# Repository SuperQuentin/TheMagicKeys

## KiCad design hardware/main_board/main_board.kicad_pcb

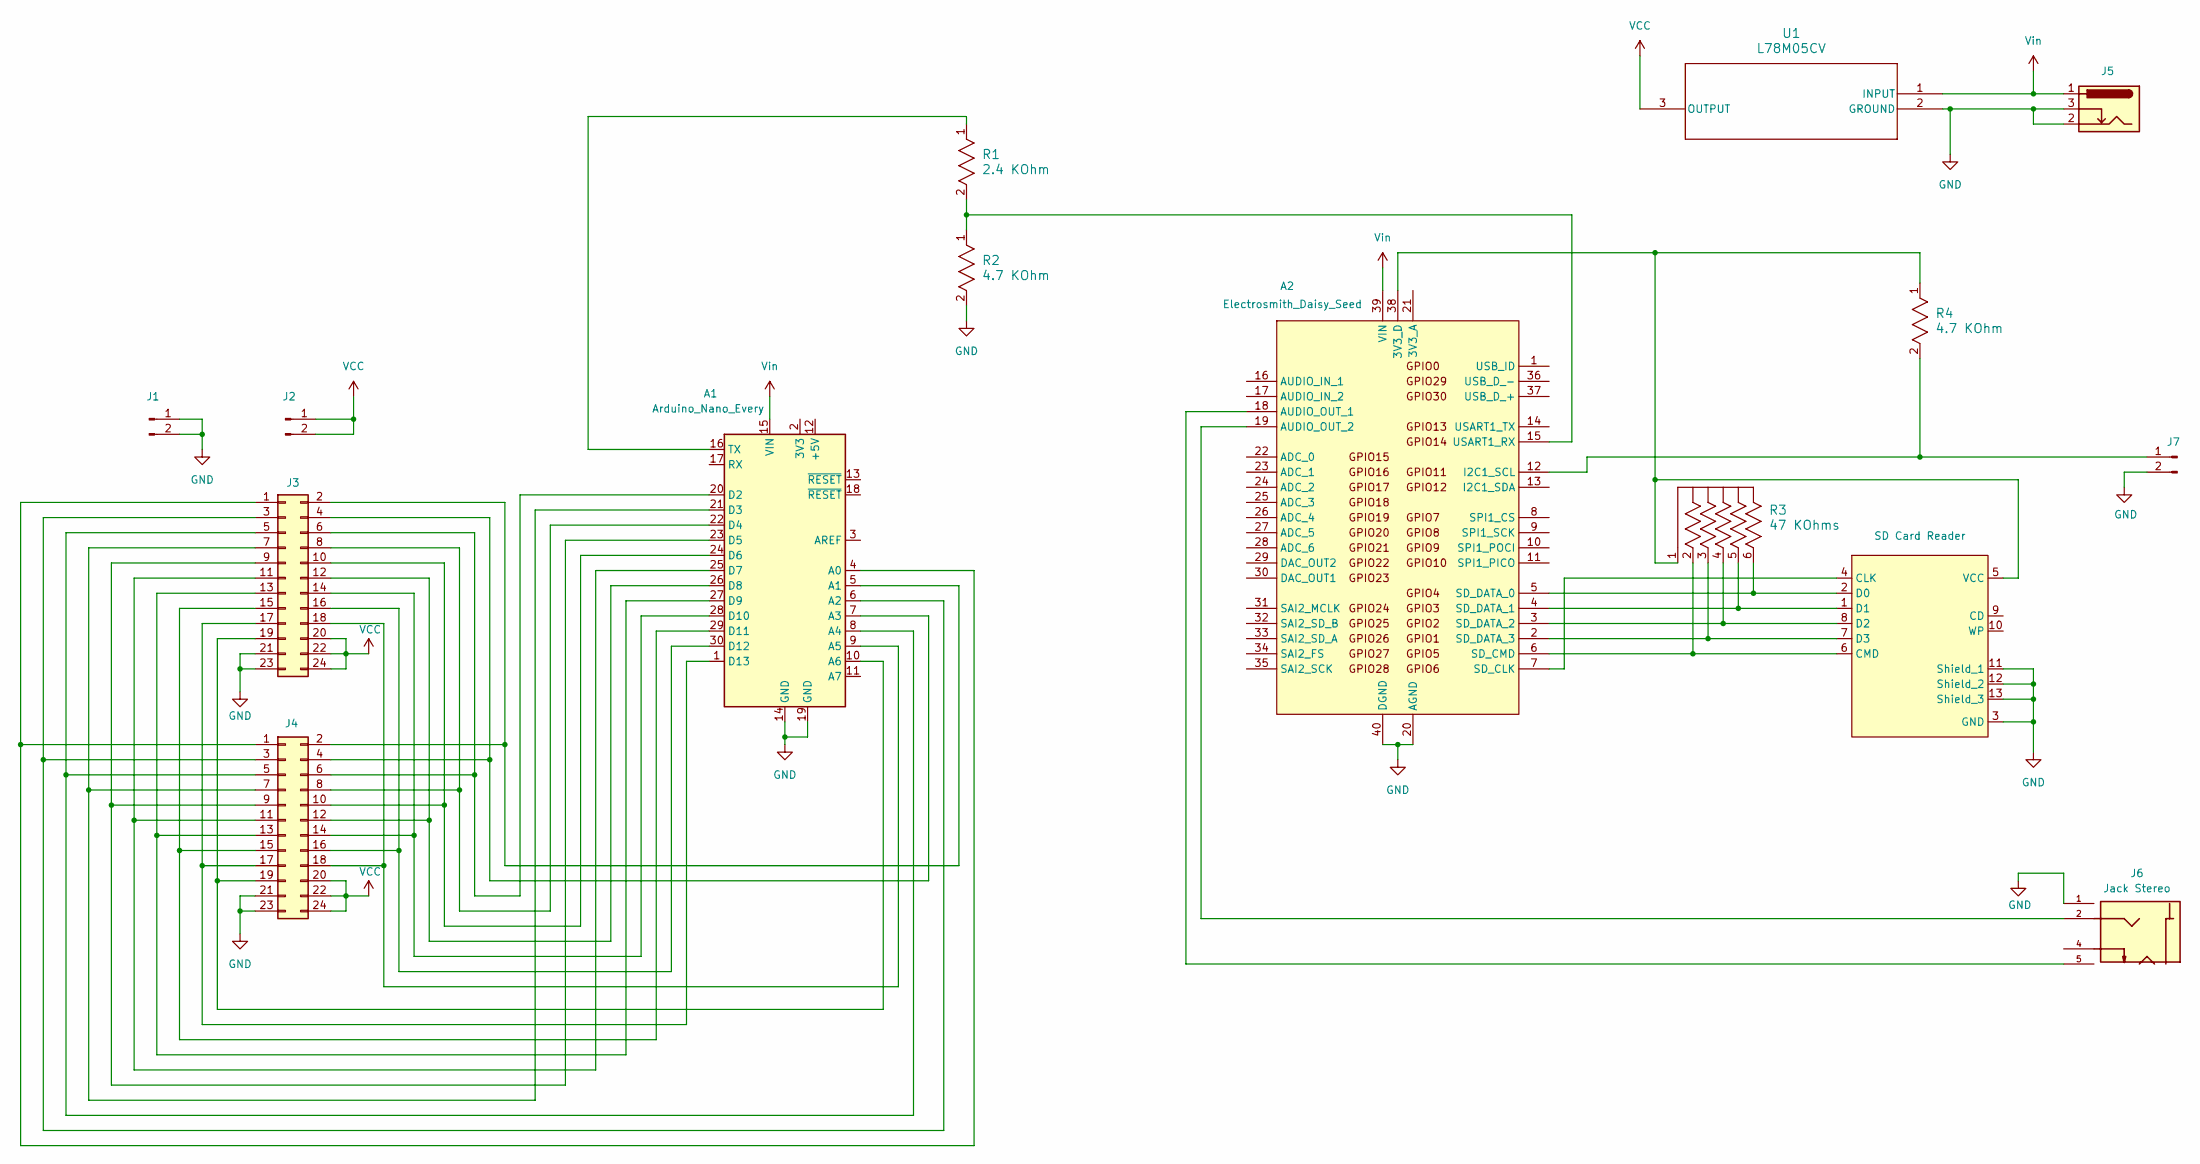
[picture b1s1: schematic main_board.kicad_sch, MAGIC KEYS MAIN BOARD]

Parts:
A1: Arduino_Nano_Every; Arduino_Nano
A2: Electrosmith_Daisy_Seed
J1, J2: PinHeader_2x01_P2.54mm_Vertical
J3, J4: Conn_02x12_Odd_Even; PinHeader_2x12_P2.54mm_Vertical
J5: Barrel_Jack_Switch_Pin2Ring; G-1005B
J6: Jack Stereo; SAMESKY_SJ3-35083C-TR; PARTREV 1.01
J7: Conn_01x02_Pin; PinHeader_1x02_P2.54mm_Vertical
R1: 2.4 KOhm; STA_CF14_STP
R2, R4: 4.7 KOhm; STA_CF14_STP
R3: 47 KOhms; BO_4606X
SDCardReaderBreakoutBoard1: SD Card Reader; SD_CARD_READER
U1: L78M05CV; TO-220_STM

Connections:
GND: A1.14 (GND), A1.19 (GND), A2.20 (AGND), A2.40 (DGND), J1.1, J1.2, J3.21, J3.23, J4.21, J4.23, J5.2, J5.3, J6.1, J7.2, R2.2, SDCardReaderBreakoutBoard1.3 (GND), SDCardReaderBreakoutBoard1.11 (Shield_1), SDCardReaderBreakoutBoard1.12 (Shield_2), SDCardReaderBreakoutBoard1.13 (Shield_3), U1.2 (GROUND)
unnamed: A1.4 (A0), J3.1, J4.1
unnamed: A1.5 (A1), J3.2, J4.2
unnamed: A1.6 (A2), J3.3, J4.3
unnamed: A1.7 (A3), J3.4, J4.4
unnamed: A1.8 (A4), J3.5, J4.5
unnamed: A1.9 (A5), J3.18, J4.18
unnamed: A1.10 (A6), J3.19, J4.19
unnamed: A1.20 (D2), J3.6, J4.6
unnamed: A1.21 (D3), J3.7, J4.7
unnamed: A1.22 (D4), J3.8, J4.8
unnamed: A1.23 (D5), J3.9, J4.9
unnamed: A1.24 (D6), J3.10, J4.10
unnamed: A1.25 (D7), J3.11, J4.11
unnamed: A1.26 (D8), J3.12, J4.12
unnamed: A1.27 (D9), J3.13, J4.13
unnamed: A1.28 (D10), J3.14, J4.14
unnamed: A1.29 (D11), J3.15, J4.15
unnamed: A1.30 (D12), J3.16, J4.16
unnamed: A1.1 (D13), J3.17, J4.17
unnamed: A1.16 (TX), R1.1
unnamed: A2.38 (3V3_D), R3.1, R4.1, SDCardReaderBreakoutBoard1.5 (VCC)
unnamed: A2.18 (AUDIO_OUT_1), J6.5
unnamed: A2.19 (AUDIO_OUT_2), J6.2
unnamed: A2.12 (I2C1_SCL), J7.1, R4.2
unnamed: A2.7 (SD_CLK), SDCardReaderBreakoutBoard1.4 (CLK)
unnamed: A2.6 (SD_CMD), R3.2, SDCardReaderBreakoutBoard1.6 (CMD)
unnamed: A2.5 (SD_DATA_0), R3.6, SDCardReaderBreakoutBoard1.2 (D0)
unnamed: A2.4 (SD_DATA_1), R3.5, SDCardReaderBreakoutBoard1.1 (D1)
unnamed: A2.3 (SD_DATA_2), R3.4, SDCardReaderBreakoutBoard1.8 (D2)
unnamed: A2.2 (SD_DATA_3), R3.3, SDCardReaderBreakoutBoard1.7 (D3)
unnamed: A2.15 (USART1_RX), R1.2, R2.1
VCC: J2.1, J2.2, J3.20, J3.22, J3.24, J4.20, J4.22, J4.24, U1.3 (OUTPUT)
Vin: A1.15 (VIN), A2.39 (VIN), J5.1, U1.1 (INPUT)

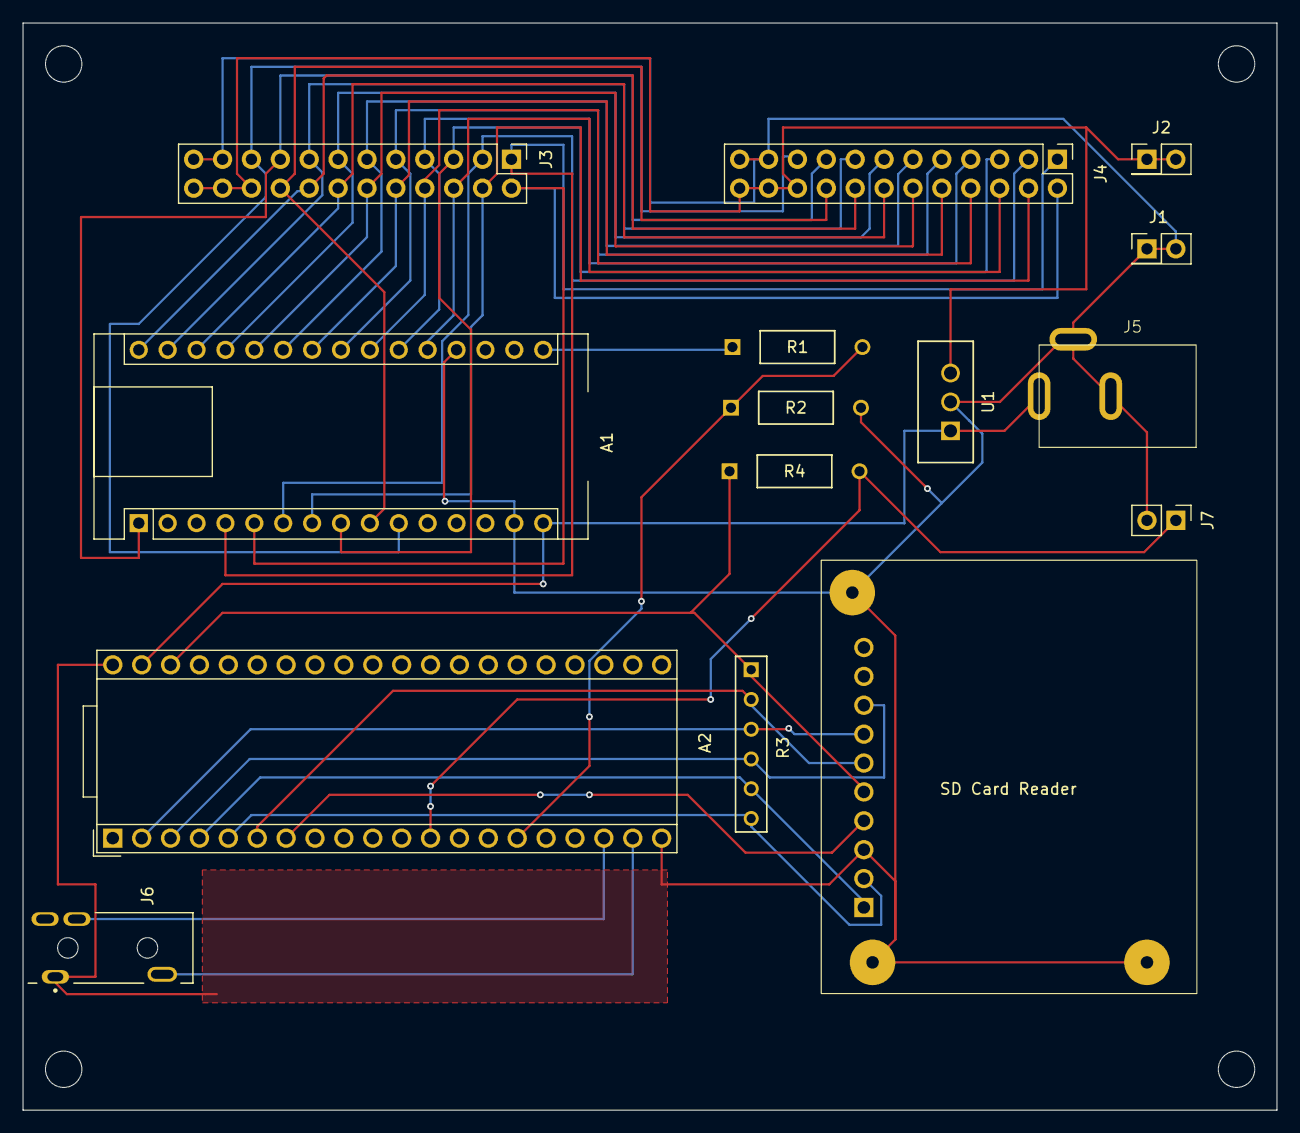
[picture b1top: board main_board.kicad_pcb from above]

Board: 2 copper layers, 110.3 x 95.6 mm, 15 parts (0 on the bottom side), 34 nets.

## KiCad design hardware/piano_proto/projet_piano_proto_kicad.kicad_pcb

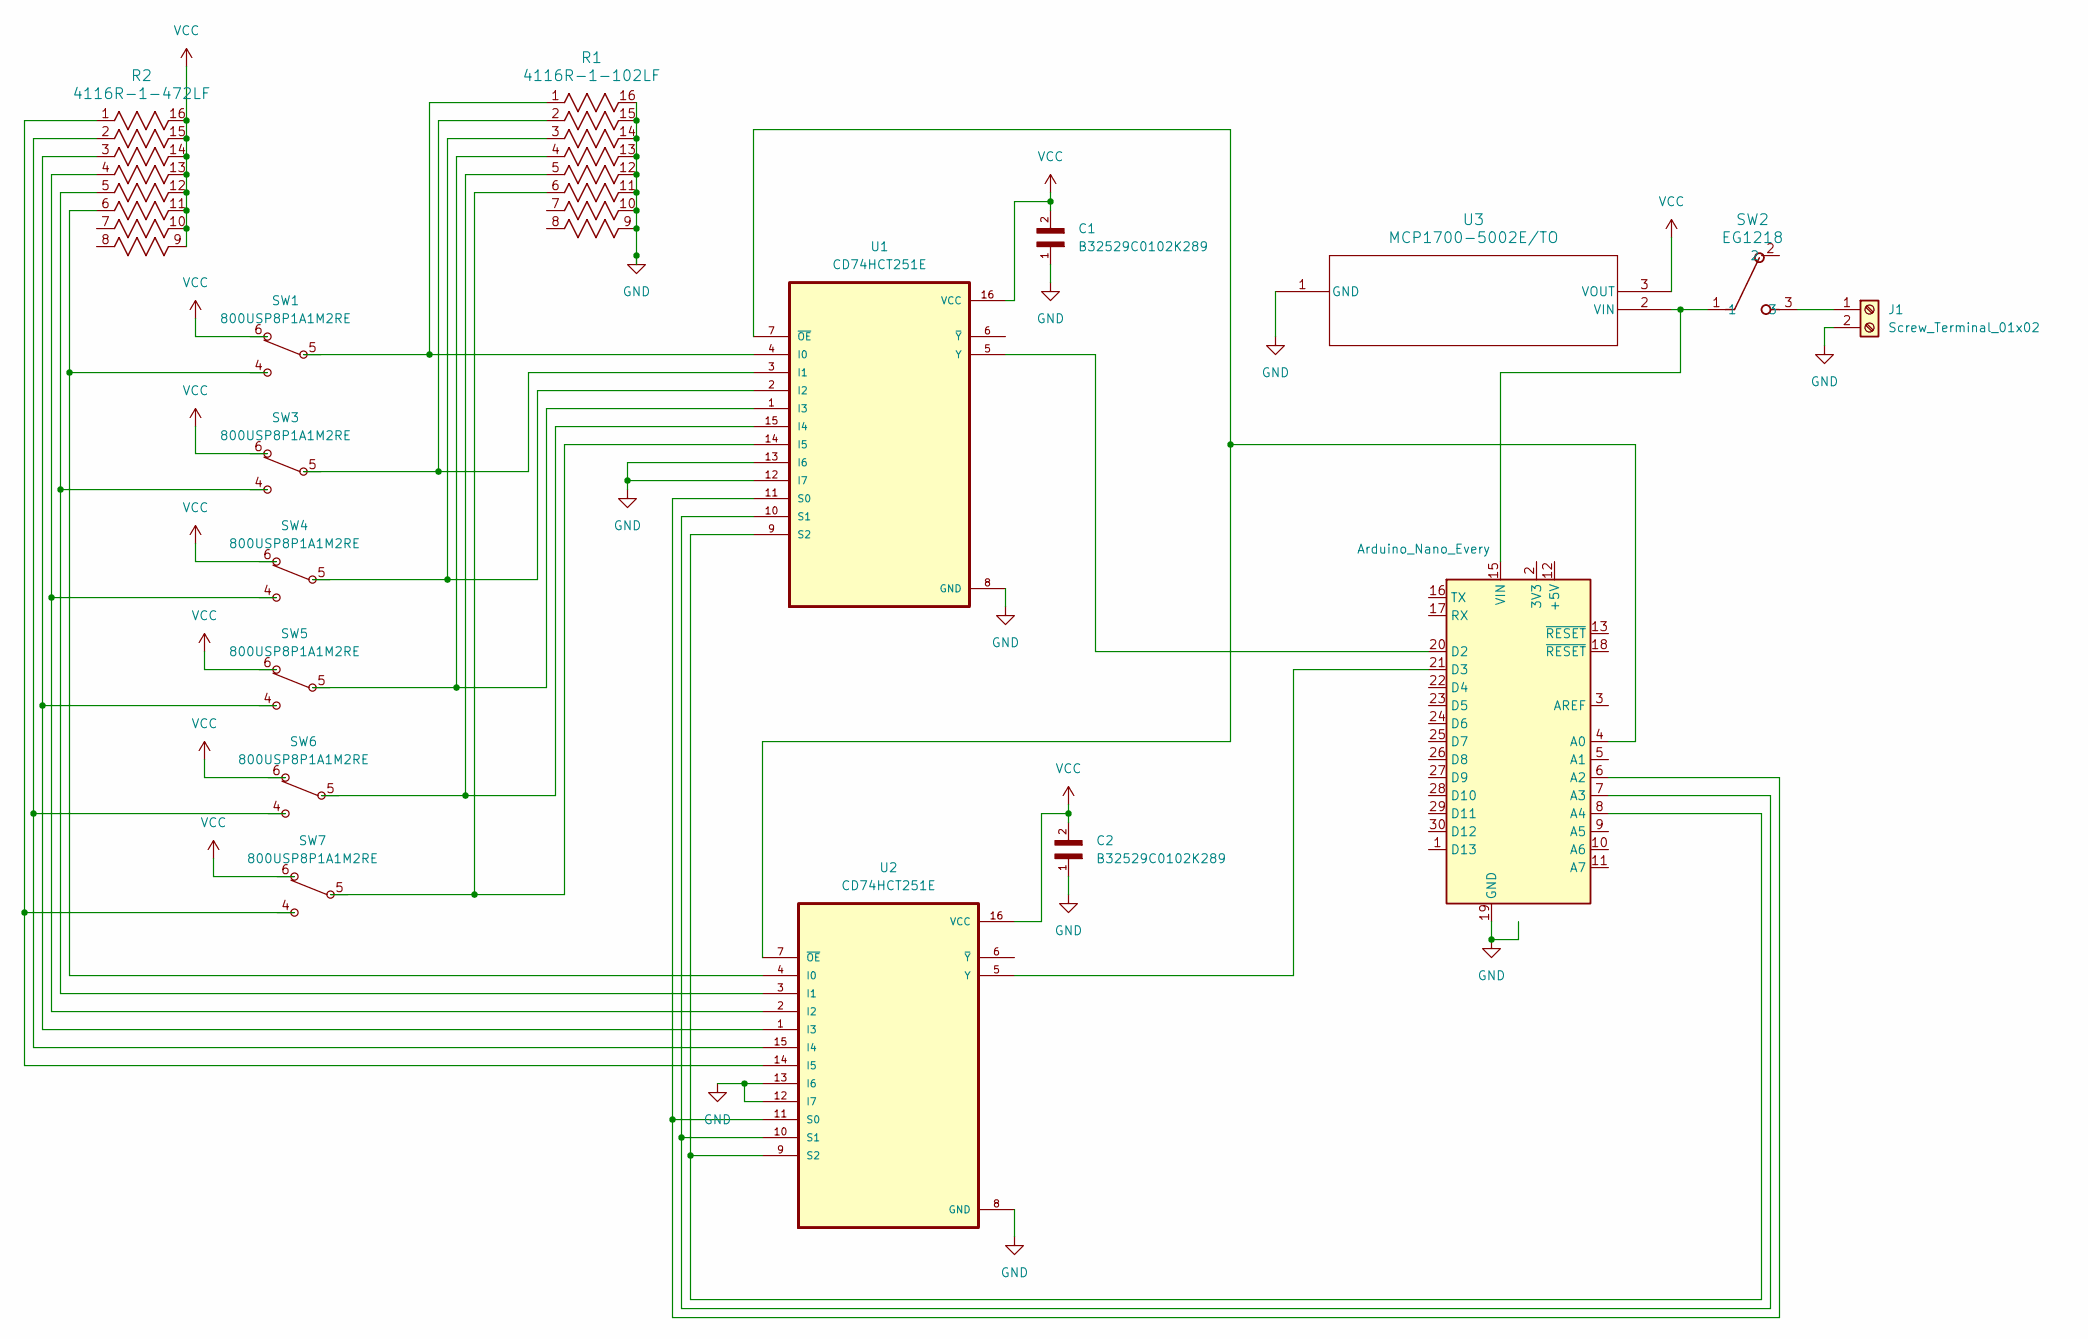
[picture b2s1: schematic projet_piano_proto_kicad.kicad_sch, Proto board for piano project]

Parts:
A2: Arduino_Nano_Every; Arduino_Nano
C1, C2: B32529C0102K289; CAPRR500W50L730T250H650; PARTREV 2020-06
J1: Screw_Terminal_01x02; TerminalBlock_Phoenix_MKDS-1,5-2-5.08_1x02_P5.08mm_Horizont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
R1: 4116R-1-102LF; BO_4116R
R2: 4116R-1-472LF; BO_4116R
SW1, SW3, SW4, SW5, SW6, SW7: 800USP8P1A1M2RE; Switch_Push_SPDT_800USP8P1A1M2RE
SW2: EG1218; SW_1218_EWI
U1, U2: CD74HCT251E; DIP794W45P254L1969H508Q16
U3: MCP1700-5002E/TO; TO-92_MC_MCH

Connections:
GND: A2.14 (GND), A2.19 (GND), C1.1, C2.1, J1.2, R1.9, R1.10, R1.11, R1.12, R1.13, R1.14, R1.15, R1.16, U1.8 (GND), U1.12 (I7), U1.13 (I6), U2.8 (GND), U2.12 (I7), U2.13 (I6), U3.1 (GND)
unnamed: A2.4 (A0), U1.7 (~OE), U2.7 (~OE)
unnamed: A2.6 (A2), U1.11 (S0), U2.11 (S0)
unnamed: A2.7 (A3), U1.10 (S1), U2.10 (S1)
unnamed: A2.20 (D2), U1.5 (Y)
unnamed: A2.21 (D3), U2.5 (Y)
unnamed: A2.8 (SDA/A4), U1.9 (S2), U2.9 (S2)
unnamed: A2.15 (VIN), SW2.1, U3.2 (VIN)
unnamed: J1.1, SW2.3
unnamed: R1.1, SW1.5 (COM), U1.4 (I0)
unnamed: R2.6, SW1.4 (NO), U2.4 (I0)
unnamed: R1.2, SW3.5 (COM), U1.3 (I1)
unnamed: R2.5, SW3.4 (NO), U2.3 (I1)
unnamed: R1.3, SW4.5 (COM), U1.2 (I2)
unnamed: R2.4, SW4.4 (NO), U2.2 (I2)
unnamed: R1.4, SW5.5 (COM), U1.1 (I3)
unnamed: R2.3, SW5.4 (NO), U2.1 (I3)
unnamed: R1.5, SW6.5 (COM), U1.15 (I4)
unnamed: R2.2, SW6.4 (NO), U2.15 (I4)
unnamed: R1.6, SW7.5 (COM), U1.14 (I5)
unnamed: R2.1, SW7.4 (NO), U2.14 (I5)
VCC: C1.2, C2.2, R2.9, R2.10, R2.11, R2.12, R2.13, R2.14, R2.15, R2.16, SW1.6 (NC), SW3.6 (NC), SW4.6 (NC), SW5.6 (NC), SW6.6 (NC), SW7.6 (NC), U1.16 (VCC), U2.16 (VCC), U3.3 (VOUT)

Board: 2 copper layers, 16 parts (0 on the bottom side), 22 nets, no tracks yet.

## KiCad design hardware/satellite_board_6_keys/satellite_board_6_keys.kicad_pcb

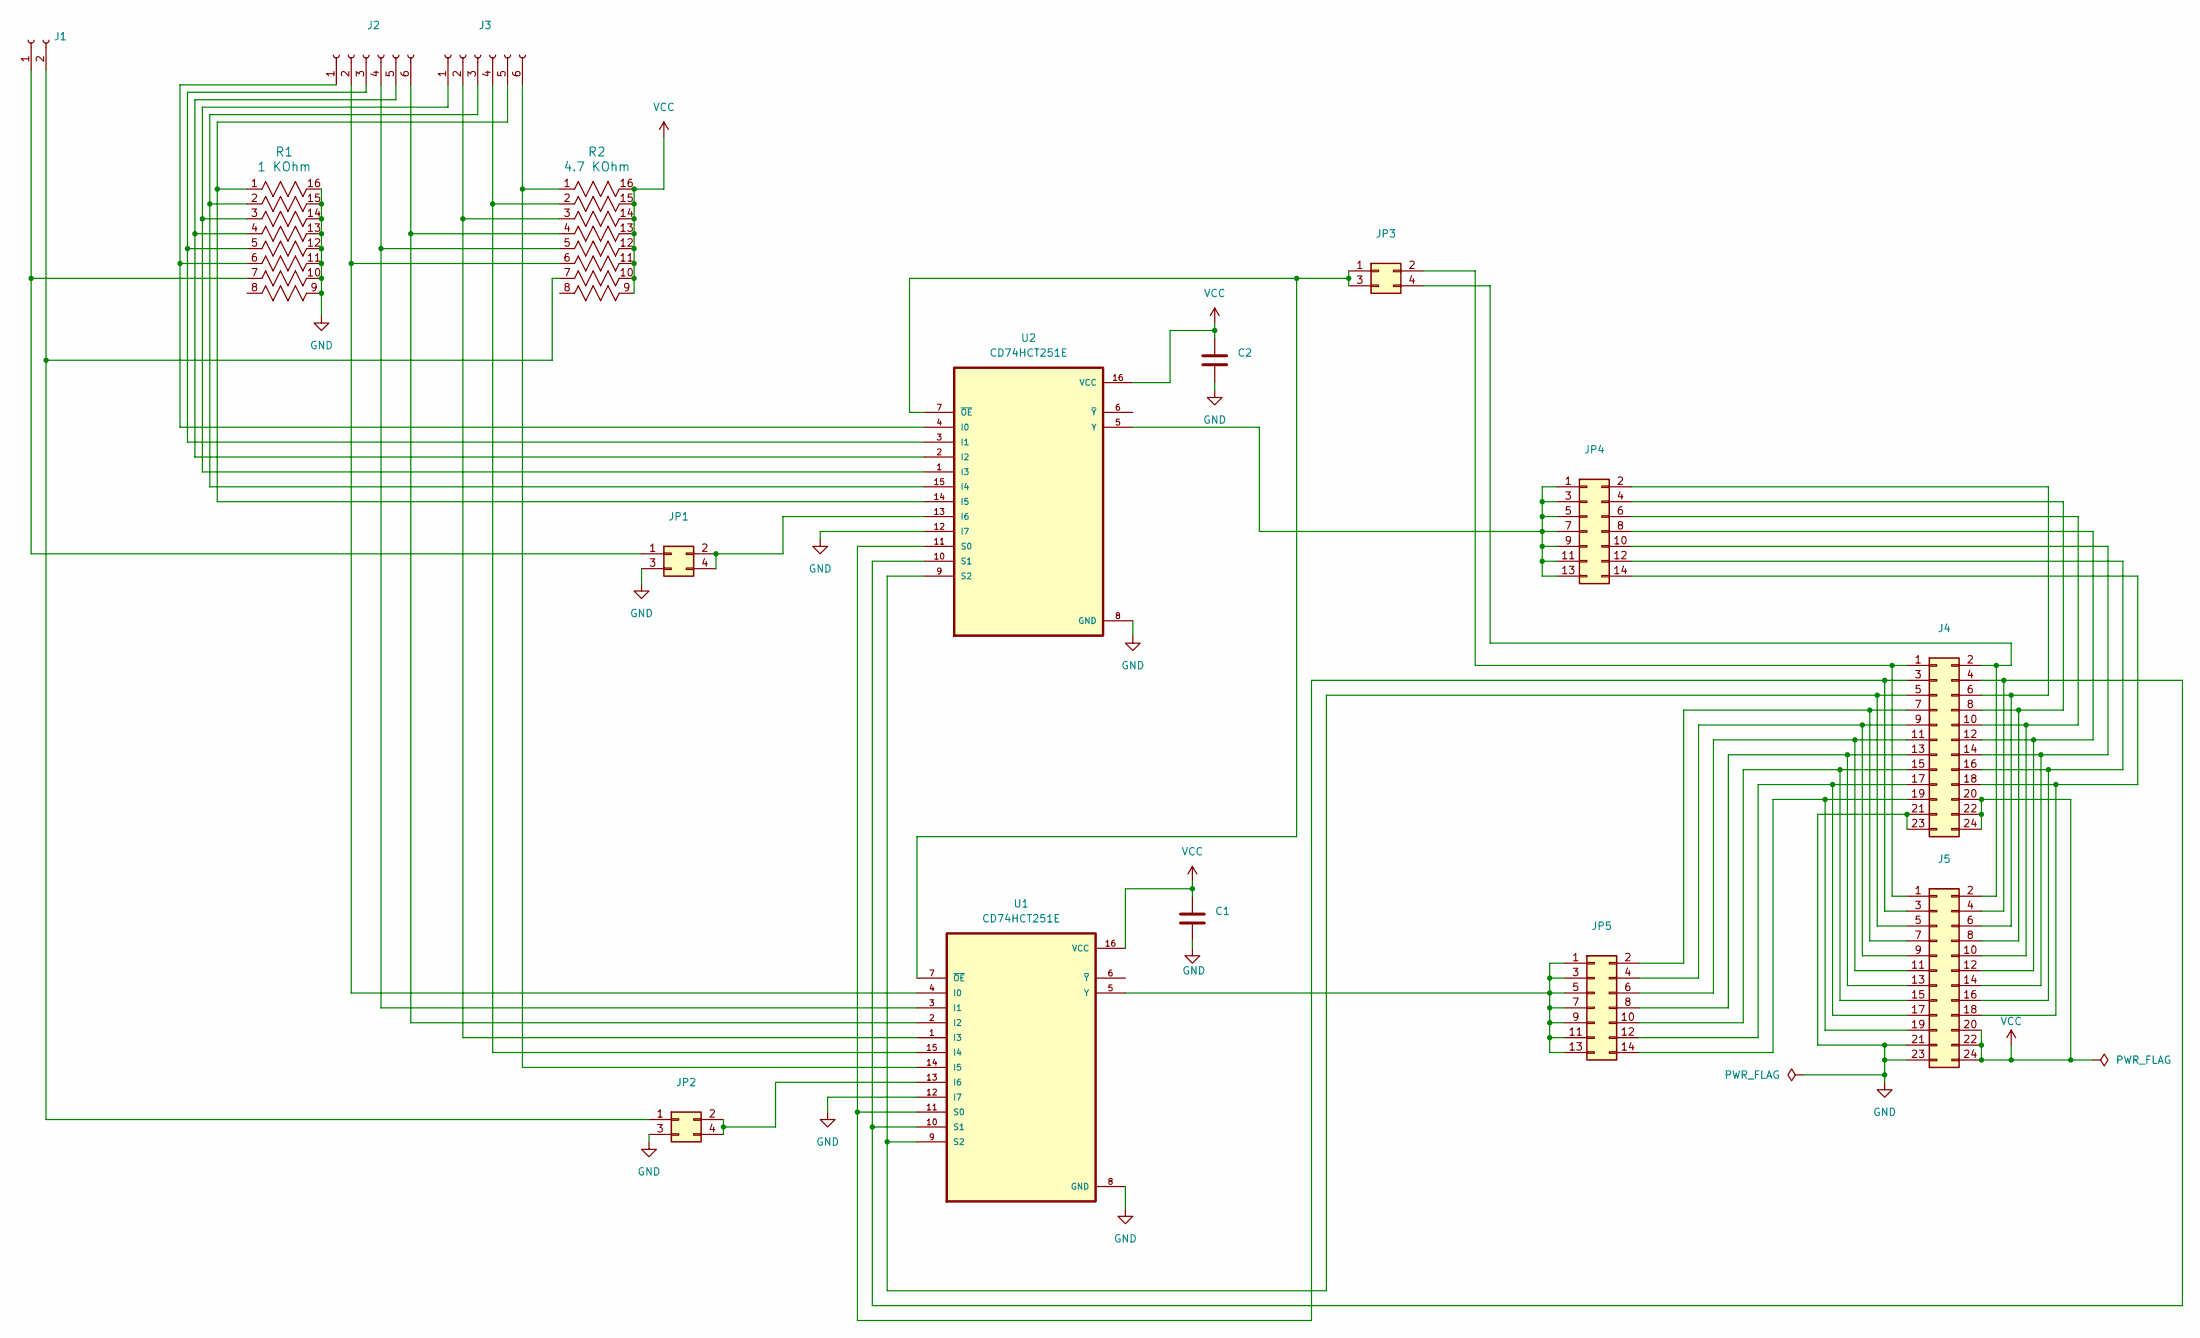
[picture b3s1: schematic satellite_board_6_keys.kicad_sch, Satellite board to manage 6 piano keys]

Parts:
C1, C2: C; CAPRR500W50L730T250H650
J1: Conn_01x02_Socket; PinHeader_1x02_P2.54mm_Vertical
J2, J3: Conn_01x06_Socket; PinHeader_1x06_P2.54mm_Vertical
J4, J5: Conn_02x12_Odd_Even; PinHeader_2x12_P2.54mm_Vertical
JP1, JP2, JP3: Conn_02x02_Odd_Even; PinHeader_2x02_P2.54mm_Vertical
JP4, JP5: Conn_02x07_Odd_Even; PinHeader_2x07_P2.54mm_Vertical
R1: 1 KOhm; BO_4116R
R2: 4.7 KOhm; BO_4116R
U1, U2: CD74HCT251E; DIP794W45P254L1969H508Q16

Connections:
GND: C1.2, C2.2, J4.21, J4.23, J5.21, J5.23, JP1.3, JP2.3, R1.9, R1.10, R1.11, R1.12, R1.13, R1.14, R1.15, R1.16, U1.8 (GND), U1.12 (I7), U2.8 (GND), U2.12 (I7)
unnamed: J1.1, JP1.1, R1.7
unnamed: J1.2, JP2.1, R2.7
unnamed: J2.1, R1.6, U2.4 (I0)
unnamed: J2.2, R2.6, U1.4 (I0)
unnamed: J2.3, R1.5, U2.3 (I1)
unnamed: J2.4, R2.5, U1.3 (I1)
unnamed: J2.5, R1.4, U2.2 (I2)
unnamed: J2.6, R2.4, U1.2 (I2)
unnamed: J3.1, R1.3, U2.1 (I3)
unnamed: J3.2, R2.3, U1.1 (I3)
unnamed: J3.3, R1.2, U2.15 (I4)
unnamed: J3.4, R2.2, U1.15 (I4)
unnamed: J3.5, R1.1, U2.14 (I5)
unnamed: J3.6, R2.1, U1.14 (I5)
unnamed: J4.1, J5.1, JP3.2
unnamed: J4.2, J5.2, JP3.4
unnamed: J4.3, J5.3, U1.11 (S0), U2.11 (S0)
unnamed: J4.4, J5.4, U1.10 (S1), U2.10 (S1)
unnamed: J4.5, J5.5, U1.9 (S2), U2.9 (S2)
unnamed: J4.6, J5.6, JP4.2
unnamed: J4.7, J5.7, JP5.2
unnamed: J4.8, J5.8, JP4.4
unnamed: J4.9, J5.9, JP5.4
unnamed: J4.10, J5.10, JP4.6
unnamed: J4.11, J5.11, JP5.6
unnamed: J4.12, J5.12, JP4.8
unnamed: J4.13, J5.13, JP5.8
unnamed: J4.14, J5.14, JP4.10
unnamed: J4.15, J5.15, JP5.10
unnamed: J4.16, J5.16, JP4.12
unnamed: J4.17, J5.17, JP5.12
unnamed: J4.18, J5.18, JP4.14
unnamed: J4.19, J5.19, JP5.14
unnamed: JP1.2, JP1.4, U2.13 (I6)
unnamed: JP2.2, JP2.4, U1.13 (I6)
unnamed: JP3.1, JP3.3, U1.7 (~OE), U2.7 (~OE)
unnamed: JP4.1, JP4.3, JP4.5, JP4.7, JP4.9, JP4.11, JP4.13, U2.5 (Y)
unnamed: JP5.1, JP5.3, JP5.5, JP5.7, JP5.9, JP5.11, JP5.13, U1.5 (Y)
VCC: C1.1, C2.1, J4.20, J4.22, J4.24, J5.20, J5.22, J5.24, R2.9, R2.10, R2.11, R2.12, R2.13, R2.14, R2.15, R2.16, U1.16 (VCC), U2.16 (VCC)

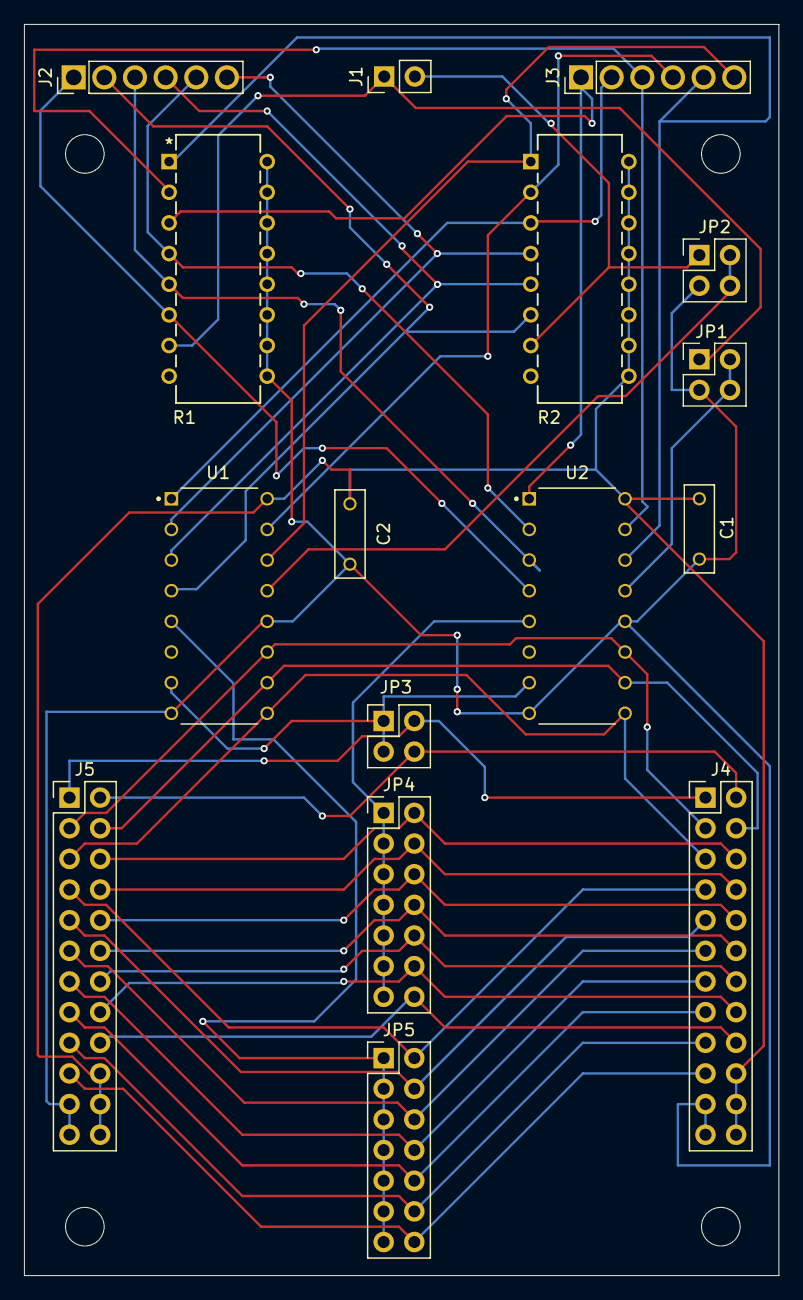
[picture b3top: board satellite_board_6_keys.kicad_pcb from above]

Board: 2 copper layers, 62.5 x 103.7 mm, 16 parts (0 on the bottom side), 40 nets.

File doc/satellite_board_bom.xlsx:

Pos | Description | Number | Detailed description | Status
1 | Multiplexer 8 channels (U1 + U2) | 2 | CD74HCT251E Digikey ref 296-2106-5-ND | In cart
2 | 8 resistors 4.7 KOhm (R1) | 1 | RES ARRAY 8 RES 4.7K OHM 16DIP DigiKey Part Number 4116R-1-472LF-ND | In cart
3 | 8 resistors 20 KOhm (R2) | 1 | RES ARRAY 8 RES 20K OHM 16DIP DigiKey Part Number 4116R-1-203LF-ND | In cart
4 | 16 pins DIL Socket | 4 | IC SOCKET, DIP, 16P 2.54MM PITCH DigiKey Ref 2057-ICS-316-T-ND | In cart
5 | capacitors 1 nF (C1 + C2) | 2 | CAP FILM 1000PF 10% 63VDC RADIAL DigiKey Ref 495-2456-1-ND - Cut Tape (CT) | In cart
6 | 2 pin male header (J1) | 1 | CONN HEADER VERT 16POS 2.54MM DigiKey Part Number 2057-PH1-16-UA-ND | In cart
7 | 2 pin female header (For J1) | 1 | CONN RCPT 32POS 0.1 TIN PCB DigiKey Part Number SAM1122-32-ND | In cart
8 | 6 pins connector from old board (J2 + J3). | 2
9 | Flat ribbon male connector 24 pins (J4 + J5) | 2 | CONN HEADER VERT 24POS 2.54MM DigiKey Part Number: 2057-BHR-24-VUA-ND | In cart
10 | Flat ribbon female connector 24 pins (for J4 + J5) | 2 | SOCKET FLAT CABLE IDC 24P 2.54MM DigiKey Part Number: 2057-FCS-24-SG-ND | In cart
11 | 2 x 2 male pin headers (JP1 + JP2 + JP3) | 3 | CONN HEADER VERT 4POS 2.54MM DigiKey Part Number: 609-5699-ND | In cart
12 | 2 x 12 male pin headers (JP3 + JP4) | 2 | CONN HEADER VERT 24POS 2.54MM DigiKey Part Number: WM50012-24-ND | In cart
13 | Jumpers (for JP1 + JP2 + JP3 + JP4 + JP5) | 5 | CONN JUMPER SHORTING .100" GOLD DigiKey Part Number: S9337-ND | In cart
14 | Flat cable 24 pins | 1 | CBL RIBN 24COND FLAT 0.05 GRAY DigiKey Part Number: 19-3365/24100-DS-ND | In cart
15 | Board spacer | 4 |  | Bought
16 | Screw | 4 |  | Bought
17 | Board 150 x 176 to fix 2 satellite boards | 0.5 |  | Bought

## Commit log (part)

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2024-11-11 batman
2024-11-12 First version after proto first tests
2024-11-13 Issue corrected: Switch 4 was not detected. Switch 2 was detected twice.
2024-12-01 Add some measurements on real keys (logical analyzer)
2024-12-01 Add some pictures
2024-12-01 Rename some pictures
2024-12-10 Add a first version of a satellite board for 6 keys. Not routed yet.
2024-12-14 First routing of the satellite board
2024-12-14 PCB order sent to manufacturer
2024-12-24 Start the main board design.
2024-12-24 [Main board] First complete schematic
2025-01-05 Improve robustness of prototype with daisy seed
2025-03-12 First test passed with main boards and all satellite boards connected
2025-03-12 Add main arduino program managing the 98 keys
2025-03-13 [Daisy Seed][key_controlled_oscillators]Instatntiate 35 oscillators. More is not possible.
2025-05-18 [DaisySeed]Add a program which plays all the notes (the range). Manage the attack and release time.
2025-05-19 [play_notes]Add some comments
2025-05-21 [Arduino]Add a program that plays the range with the daisy seed. [Daisy seed]Add a program that play the notes received from the Arduino
2025-05-21 [Daisy Seed]Now takes into account the key velocity to compute the note volume.
2025-06-15 Test the synthetizer by reading a midi file
2025-08-02 Modifications after tests on the real piano. Remap the keys correctly (7th key not connected on Satellite boards). Disable release time because otherwise same notes cannot be played again rapidly. Tu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
2025-09-13 Finish main board PCB
2025-09-15 Bug corrected: Don't use on board LED, it is connected to D12 + Add a program that displays the state of the 98 keys
2025-10-03 Add the pedal management
2025-10-04 [DaisySeed]Improve program comment and structure.
2025-10-04 [Arduino]Update program used for troubleshooting.
2025-10-05 [DaisySeed]Avoid the click sound at the end of the note (when the note is played until the end).
2025-10-06 [Daisyseed] Issue corrected: When the note was played until the end a click sound appears when the key or the pedal was released.
2025-10-18 [DaisySeed][play_notes_from_arduino]Add management of special sounds. Play sound ready at the end of initialisation.
2025-10-18 [DaisySeed][play_notes_from_arduino][Program mode management]Work in progress
2025-11-01 [DaisySeed][play_notes_from_arduino][Program mode management]Program selection is now functionnal if a power cycle is applied between program change.
2025-11-02 [DaisySeed][play_notes_from_arduino][Program mode management]Program selection is now functionnal without power recycle + Global variables have been renamed.
2025-11-02 [DaisySeed][play_notes_from_arduino][Program mode management]Play sounds at start an end of programmation
2025-11-02 [DaisySeed][play_notes_from_arduino]Add log modes.
2025-11-07 Add wav files used
2025-11-09 Add demo mode to play midi files
2025-11-09 Move the code to play midi files in a dedicated module
2025-11-11 Put the code to play midi file in a different module
2025-11-11 Improve play_midi_file
2025-11-30 Issue corrected: program index was wrong
2025-11-30 [WAV][Grand Piano]Use notesC A0..A7 instead of C1..C8
2025-11-30 Rename wav zip
2025-11-30 [WAV][Old piano]Generate notes A0..A7 instead of C1..C8
2025-12-04 [WAV]Add Harp
2025-12-06 [WAV]Add Rock Organ
